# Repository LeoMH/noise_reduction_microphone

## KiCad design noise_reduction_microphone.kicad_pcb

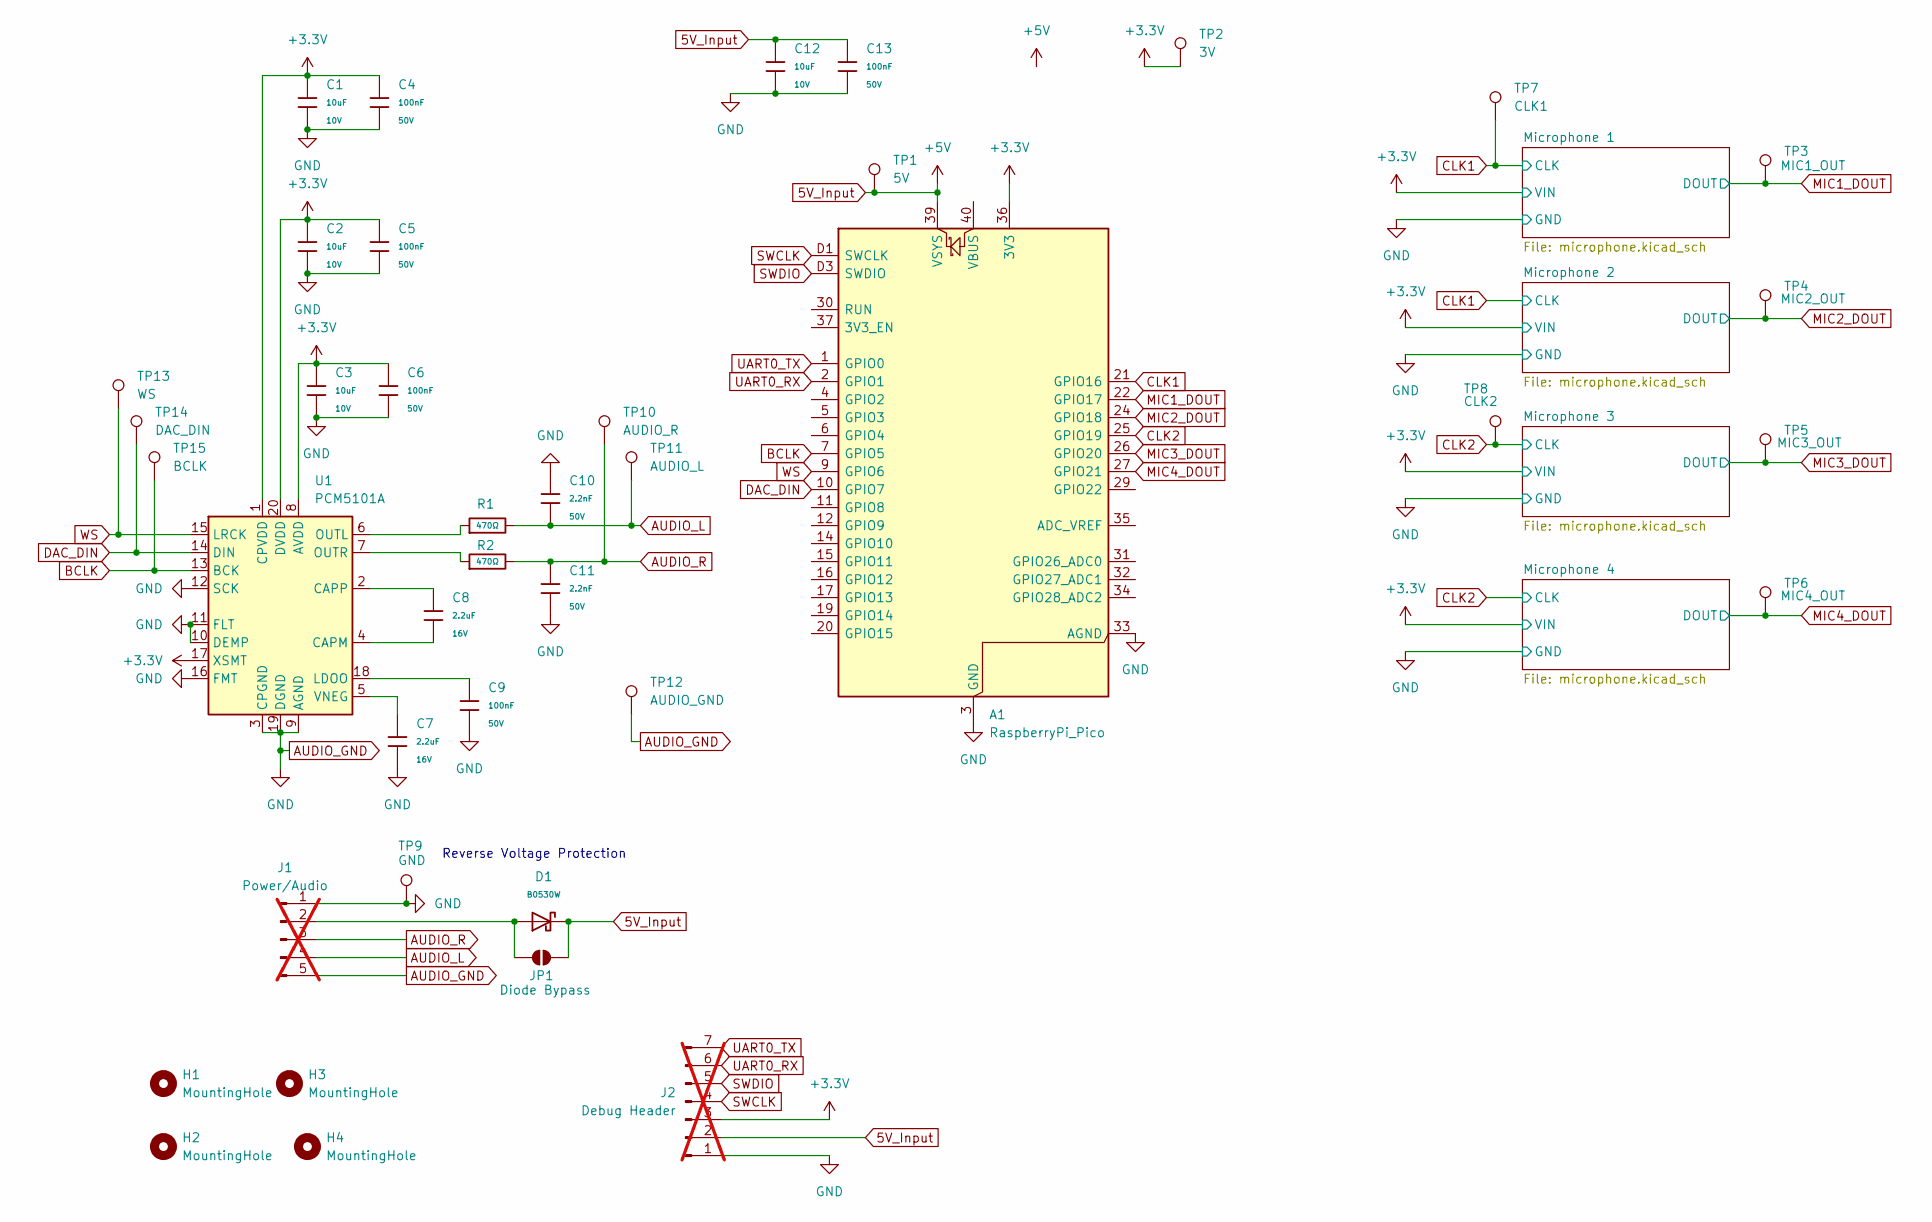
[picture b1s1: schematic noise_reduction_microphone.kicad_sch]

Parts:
A1: RaspberryPi_Pico; RaspberryPi_Pico_SMD_HandSolder
C1, C2, C3, C12: 10uF; C_0603; Voltage Rated 10V; Tolerance ±10%; Part CL10A106KP8NNNC; LCSC C19702
C4, C5, C6, C9, C13: 100nF; C_0603; Voltage Rated 50V; Tolerance ±10%; Part CC0603KRX7R9BB104; LCSC C14663
C7, C8: 2.2uF; C_0603; Voltage Rated 16V; Tolerance ±10%; Part CL10A225KO8NNNC; LCSC C23630
C10, C11: 2.2nF; C_0603; Voltage Rated 50V; Tolerance ±10%; Part 0603B222K500NT; LCSC C1604
D1: B0530W; D_SOD-123; Part B0530W; LCSC C7502708
H1, H2, H3, H4: MountingHole; MountingHole_3mm
J1: Power/Audio; PinHeader_1x05_P2.54mm_Vertical; not fitted
J2: Debug Header; PinHeader_1x07_P2.54mm_Vertical; not fitted
JP1: Diode Bypass; SolderJumper-2_P1.3mm_Open_RoundedPad1.0x1.5mm
R1, R2: 470Ω; R_0603; Overload Voltage (Max) 75V; Tolerance ±1%; Part 0603WAF4700T5E; LCSC C23179
TP1: 5V; TestPoint_Pad_D2.0mm
TP2: 3V; TestPoint_Pad_D2.0mm
TP3: MIC1_OUT; TestPoint_Pad_D2.0mm
TP4: MIC2_OUT; TestPoint_Pad_D2.0mm
TP5: MIC3_OUT; TestPoint_Pad_D2.0mm
TP6: MIC4_OUT; TestPoint_Pad_D2.0mm
TP7: CLK1; TestPoint_Pad_D2.0mm
TP8: CLK2; TestPoint_Pad_D2.0mm
TP9: GND; TestPoint_Pad_D2.0mm
TP10: AUDIO_R; TestPoint_Pad_D2.0mm
TP11: AUDIO_L; TestPoint_Pad_D2.0mm
TP12: AUDIO_GND; TestPoint_Pad_D2.0mm
TP13: WS; TestPoint_Pad_D2.0mm
TP14: DAC_DIN; TestPoint_Pad_D2.0mm
TP15: BCLK; TestPoint_Pad_D2.0mm
U1: PCM5101A; TSSOP-20_4.4x6.5mm_P0.65mm; LCSC Part # C1540128

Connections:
5V_Input: A1.39 (VSYS), C12.1, C13.1, D1.1, J2.2, JP1.2 (B), TP1.1
+3.3V: A1.36 (3V3), C1.1, C2.1, C3.1, C4.1, C5.1, C6.1, J2.3, TP2.1, U1.1 (CPVDD), U1.8 (AVDD), U1.17 (XSMT), U1.20 (DVDD); also elsewhere on the board
AUDIO_GND: A1.3 (GND), A1.8 (GND), A1.13 (GND), A1.18 (GND), A1.23 (GND), A1.28 (GND), A1.33 (AGND), A1.38 (GND), A1.D2 (GND), C1.2, C2.2, C3.2, C4.2, C5.2, C6.2, C7.2, C9.2, C10.1, C11.2, C12.2, C13.2, J1.1, J1.5, J2.1, TP9.1, TP12.1, U1.3 (CPGND), U1.9 (AGND), U1.10 (DEMP), U1.11 (FLT), U1.12 (SCK), U1.16 (FMT), U1.19 (DGND); also elsewhere on the board
AUDIO_L: C10.2, J1.4, R1.2, TP11.1
AUDIO_R: C11.1, J1.3, R2.2, TP10.1
BCLK: A1.7 (GPIO5), TP15.1, U1.13 (BCK)
CLK1: A1.21 (GPIO16), TP7.1; also elsewhere on the board
CLK2: A1.25 (GPIO19), TP8.1; also elsewhere on the board
DAC_DIN: A1.10 (GPIO7), TP14.1, U1.14 (DIN)
MIC1_DOUT: A1.22 (GPIO17), TP3.1; also elsewhere on the board
MIC2_DOUT: A1.24 (GPIO18), TP4.1; also elsewhere on the board
MIC3_DOUT: A1.26 (GPIO20), TP5.1; also elsewhere on the board
MIC4_DOUT: A1.27 (GPIO21), TP6.1; also elsewhere on the board
unnamed: D1.2, J1.2, JP1.1 (A)
unnamed: C8.2, U1.4 (CAPM)
unnamed: C8.1, U1.2 (CAPP)
unnamed: C9.1, U1.18 (LDOO)
unnamed: R1.1, U1.6 (OUTL)
unnamed: R2.1, U1.7 (OUTR)
unnamed: C7.1, U1.5 (VNEG)
SWCLK: A1.D1 (SWCLK), J2.4
SWDIO: A1.D3 (SWDIO), J2.5
UART0_RX: A1.2 (GPIO1), J2.6
UART0_TX: A1.1 (GPIO0), J2.7
WS: A1.9 (GPIO6), TP13.1, U1.15 (LRCK)

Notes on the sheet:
Reverse Voltage Protection

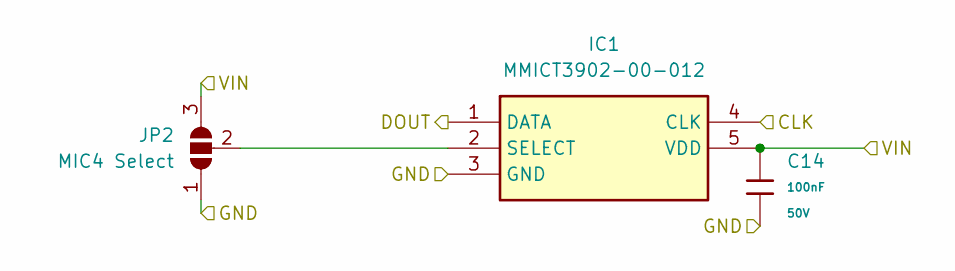
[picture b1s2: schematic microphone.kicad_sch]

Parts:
C14: 100nF; C_0603; Voltage Rated 50V; Tolerance ±10%; Part CC0603KRX7R9BB104; LCSC C14663
IC1: MMICT3902-00-012; MMICT390200012; Manufacturer_Part_Number MMICT3902-00-012; Mouser Part Number 410-MMICT3902-00-012
JP2: MIC4 Select; SolderJumper-3_P1.3mm_Open_RoundedPad1.0x1.5mm

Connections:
+3.3V: C14.1, IC1.5 (VDD), JP2.3 (B); also elsewhere on the board
AUDIO_GND: C14.2, IC1.3 (GND), JP2.1 (A); also elsewhere on the board
CLK1: IC1.4 (CLK); also elsewhere on the board
MIC1_DOUT: IC1.1 (DATA); also elsewhere on the board
unnamed: IC1.2 (SELECT), JP2.2 (C)

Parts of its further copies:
C15, C16, C17: 100nF; C_0603; Voltage Rated 50V; Tolerance ±10%; Part CC0603KRX7R9BB104; LCSC C14663
IC2, IC3, IC4: MMICT3902-00-012; MMICT390200012; Manufacturer_Part_Number MMICT3902-00-012; Mouser Part Number 410-MMICT3902-00-012
JP3, JP4, JP5: MIC4 Select; SolderJumper-3_P1.3mm_Open_RoundedPad1.0x1.5mm

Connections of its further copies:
+3.3V: C15.1, C16.1, C17.1, IC2.5 (VDD), IC3.5 (VDD), IC4.5 (VDD), JP3.3 (B), JP4.3 (B), JP5.3 (B); also elsewhere on the board
AUDIO_GND: C15.2, C16.2, C17.2, IC2.3 (GND), IC3.3 (GND), IC4.3 (GND), JP3.1 (A), JP4.1 (A), JP5.1 (A); also elsewhere on the board
CLK1: IC2.4 (CLK); also elsewhere on the board
CLK2: IC3.4 (CLK), IC4.4 (CLK); also elsewhere on the board
MIC2_DOUT: IC2.1 (DATA); also elsewhere on the board
MIC3_DOUT: IC3.1 (DATA); also elsewhere on the board
MIC4_DOUT: IC4.1 (DATA); also elsewhere on the board
unnamed: IC2.2 (SELECT), JP3.2 (C)
unnamed: IC3.2 (SELECT), JP4.2 (C)
unnamed: IC4.2 (SELECT), JP5.2 (C)

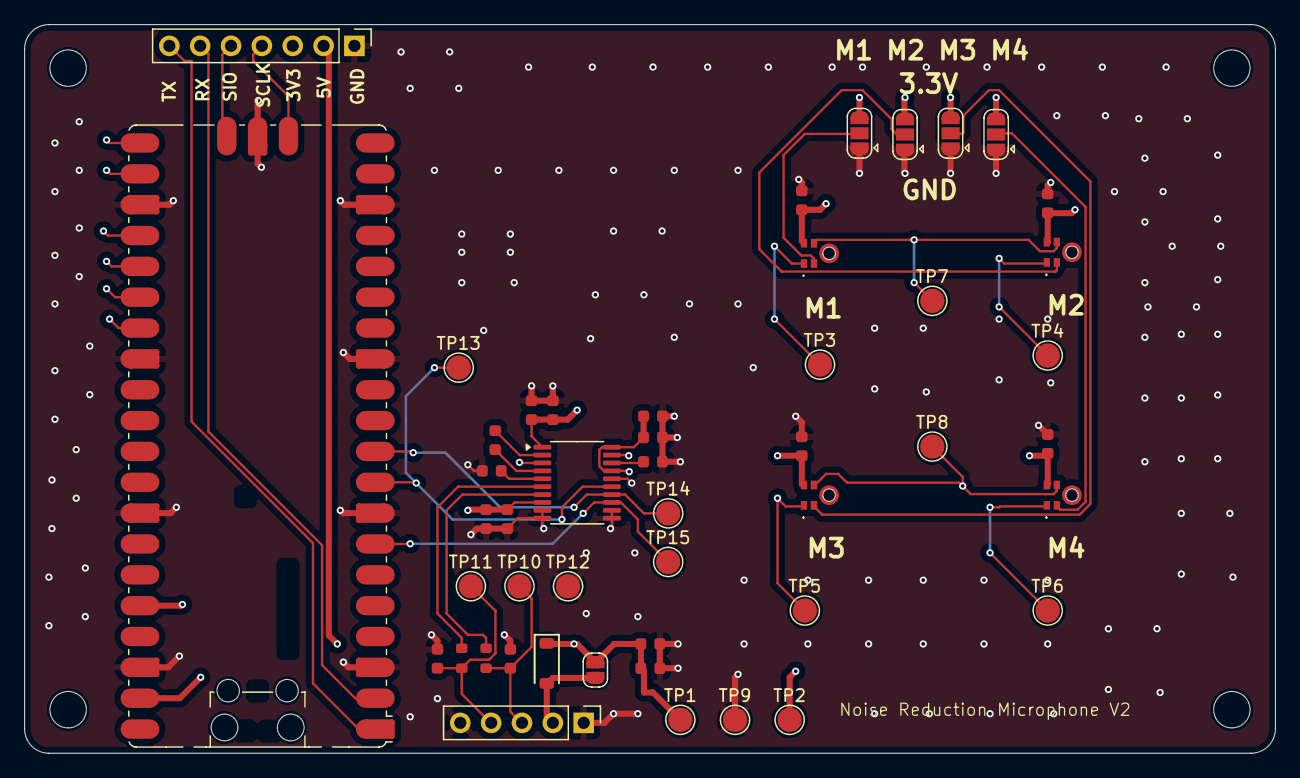
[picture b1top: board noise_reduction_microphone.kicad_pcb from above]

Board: 4 copper layers, 103.0 x 60.0 mm, 52 parts (0 on the bottom side), 29 nets.

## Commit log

2025-10-24 Added test points and another connector for audio gnd
2025-10-24 Hide values on fab layer
